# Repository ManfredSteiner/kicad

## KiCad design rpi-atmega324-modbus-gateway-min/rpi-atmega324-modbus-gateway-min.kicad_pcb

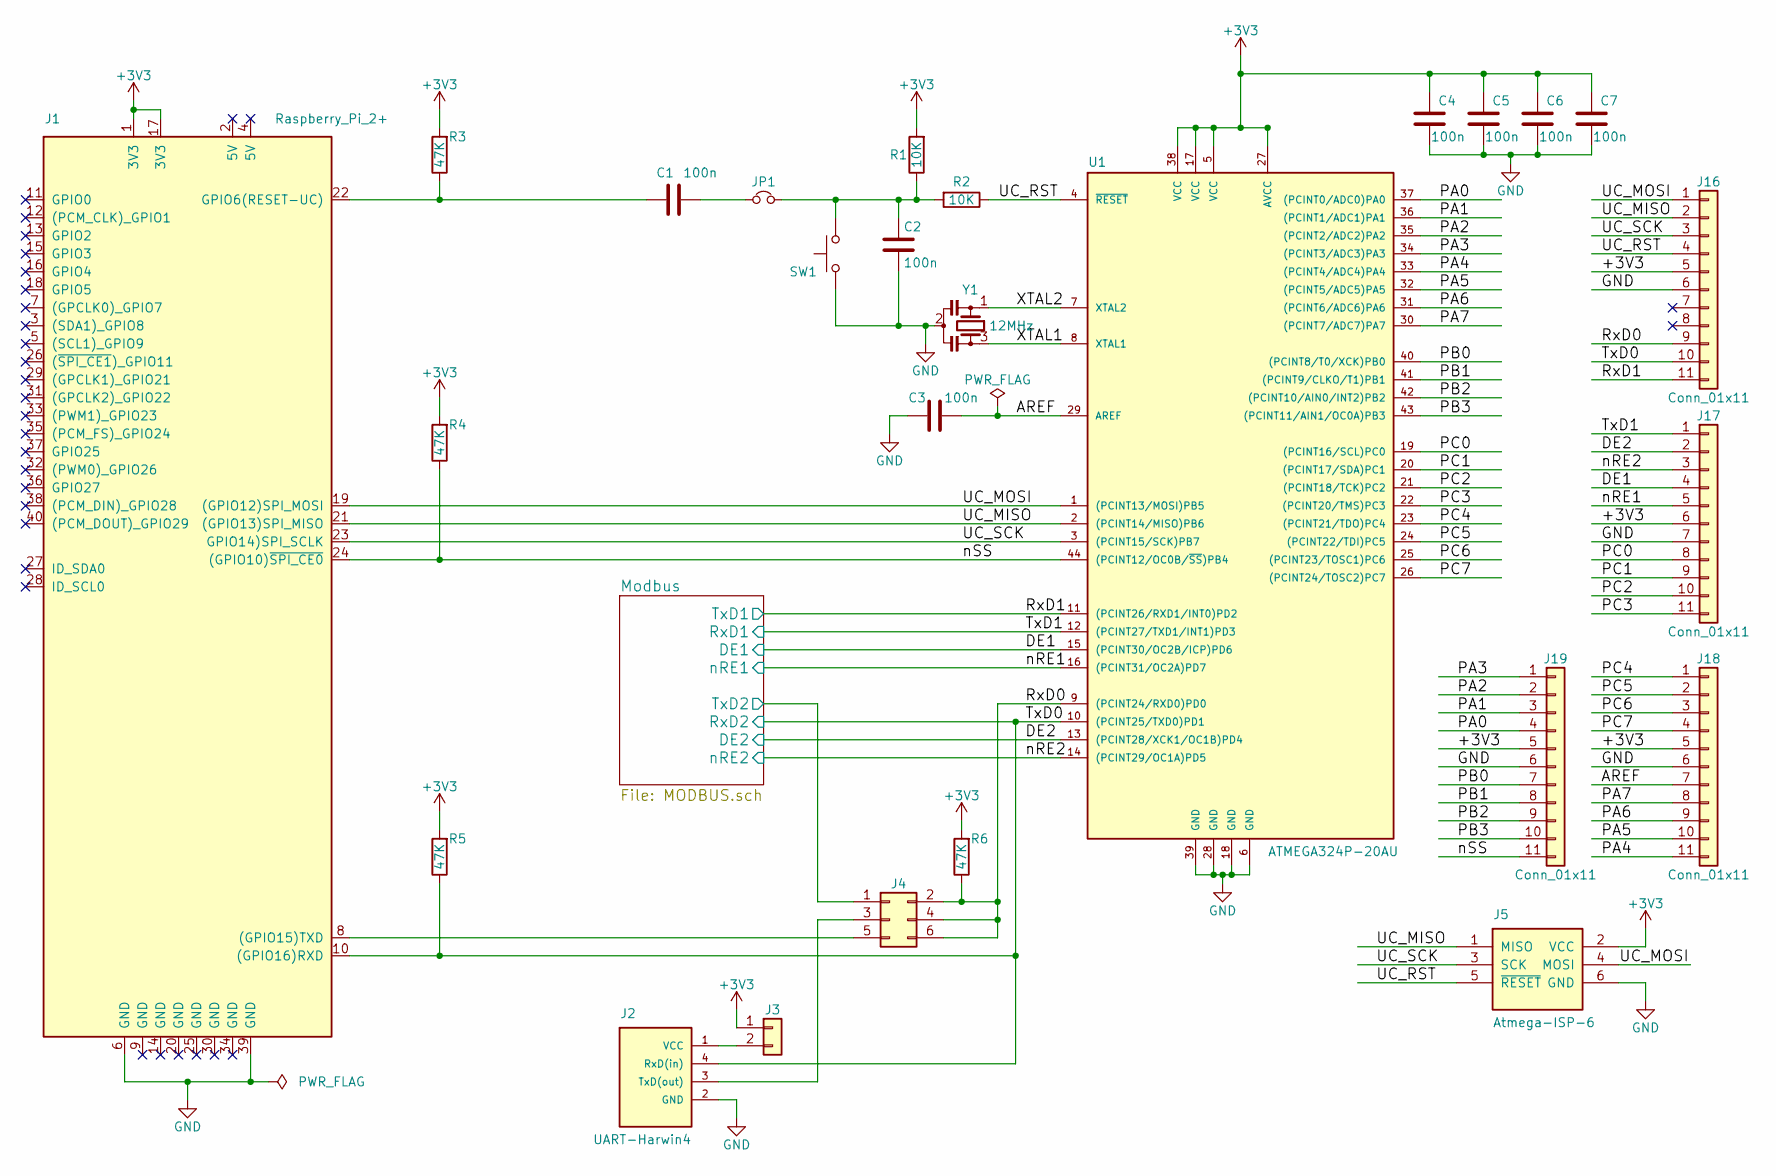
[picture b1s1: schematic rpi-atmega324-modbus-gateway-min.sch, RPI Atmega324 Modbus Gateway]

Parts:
C1, C2, C3, C4, C5, C6, C7: 100n; C_1206_HandSoldering
J1: Raspberry_Pi_2+; RPI_DINRAILBOX_4TE_72mmx91mm_DEBUG
J2: UART-Harwin4; Harwin_LTek-Male_04x2.00mm_Straight_StrainRelief
J3: Conn_01x02; Pin_Header_Straight_1x02_Pitch2.54mm
J4: Conn_02x03_Odd_Even; Pin_Header_Straight_2x03_Pitch2.54mm
J5: Atmega-ISP-6; IDC_2x3x2.54mm_Straight
J16, J17, J18, J19: Conn_01x11; Pin_Header_Straight_1x11_Pitch2.54mm
JP1: Jumper_NC_Small; SOLDER-JUMPER_1-WAY
R1, R2: 10K; R_1206_HandSoldering
R3, R4, R5, R6: 47K; R_1206_HandSoldering
SW1: SW_Push; SW_SPST_FSMSM
U1: ATMEGA324P-20AU; TQFP-44_10x10mm_Pitch0.8mm
Y1: 12MHz; Resonator-3pin_w7.0mm_h2.5mm

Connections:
+3V3: C4.2, C5.2, C6.2, C7.2, J1.1 (3V3), J1.17 (3V3), J3.1, J5.2 (VCC), J16.5, J17.6, J18.5, J19.5, R1.2, R3.2, R4.2, R5.2, R6.2, U1.5 (VCC), U1.17 (VCC), U1.27 (AVCC), U1.38 (VCC); also elsewhere on the board
/AREF: C3.1, J18.7, U1.29 (AREF)
/DE1: J17.4, U1.15 ((PCINT30/OC2B/ICP)PD6); also elsewhere on the board
/DE2: J17.2, U1.13 ((PCINT28/XCK1/OC1B)PD4); also elsewhere on the board
/Modbus/TxD2: J4.1; also elsewhere on the board
/PA0: J19.4, U1.37 ((PCINT0/ADC0)PA0)
/PA1: J19.3, U1.36 ((PCINT1/ADC1)PA1)
/PA2: J19.2, U1.35 ((PCINT2/ADC2)PA2)
/PA3: J19.1, U1.34 ((PCINT3/ADC3)PA3)
/PA4: J18.11, U1.33 ((PCINT4/ADC4)PA4)
/PA5: J18.10, U1.32 ((PCINT5/ADC5)PA5)
/PA6: J18.9, U1.31 ((PCINT6/ADC6)PA6)
/PA7: J18.8, U1.30 ((PCINT7/ADC7)PA7)
/PB0: J19.7, U1.40 ((PCINT8/T0/XCK)PB0)
/PB1: J19.8, U1.41 ((PCINT9/CLKO/T1)PB1)
/PB2: J19.9, U1.42 ((PCINT10/AIN0/INT2)PB2)
/PB3: J19.10, U1.43 ((PCINT11/AIN1/OC0A)PB3)
/PC0: J17.8, U1.19 ((PCINT16/SCL)PC0)
/PC1: J17.9, U1.20 ((PCINT17/SDA)PC1)
/PC2: J17.10, U1.21 ((PCINT18/TCK)PC2)
/PC3: J17.11, U1.22 ((PCINT20/TMS)PC3)
/PC4: J18.1, U1.23 ((PCINT21/TDO)PC4)
/PC5: J18.2, U1.24 ((PCINT22/TDI)PC5)
/PC6: J18.3, U1.25 ((PCINT23/TOSC1)PC6)
/PC7: J18.4, U1.26 ((PCINT24/TOSC2)PC7)
/RxD0: J4.2, J4.4, J4.6, J16.9, R6.1, U1.9 ((PCINT24/RXD0)PD0)
/RxD1: J16.11, U1.11 ((PCINT26/RXD1/INT0)PD2); also elsewhere on the board
/TxD0: J1.10 ((GPIO16)RXD), J2.4 (RxD(in)), J16.10, R5.1, U1.10 ((PCINT25/TXD0)PD1); also elsewhere on the board
/TxD1: J17.1, U1.12 ((PCINT27/TXD1/INT1)PD3); also elsewhere on the board
/UC_MISO: J1.21 ((GPIO13)SPI_MISO), J5.1 (MISO), J16.2, U1.2 ((PCINT14/MISO)PB6)
/UC_MOSI: J1.19 ((GPIO12)SPI_MOSI), J5.4 (MOSI), J16.1, U1.1 ((PCINT13/MOSI)PB5)
/UC_RST: J5.5 (~RESET~), J16.4, R2.1, U1.4 (~RESET)
/UC_SCK: J1.23 (GPIO14)SPI_SCLK), J5.3 (SCK), J16.3, U1.3 ((PCINT15/SCK)PB7)
/XTAL1: U1.8 (XTAL1), Y1.3
/XTAL2: U1.7 (XTAL2), Y1.1
/nRE1: J17.5, U1.16 ((PCINT31/OC2A)PD7); also elsewhere on the board
/nRE2: J17.3, U1.14 ((PCINT29/OC1A)PD5); also elsewhere on the board
/nSS: J1.24 ((GPIO10)~SPI_CE0~), J19.11, R4.1, U1.44 ((PCINT12/OC0B/~SS~)PB4)
GND: C2.2, C3.2, C4.1, C5.1, C6.1, C7.1, J1.6 (GND), J1.39 (GND), J2.2 (GND), J5.6 (GND), J16.6, J17.7, J18.6, J19.6, SW1.1, U1.6 (GND), U1.18 (GND), U1.28 (GND), U1.39 (GND), Y1.2; also elsewhere on the board
unnamed: C1.1, JP1.1
unnamed: C1.2, J1.22 (GPIO6(RESET-UC)), R3.1
unnamed: C2.1, JP1.2, R1.1, R2.2, SW1.2
unnamed: J1.8 ((GPIO15)TXD), J4.5
unnamed: J2.1 (VCC), J3.2
unnamed: J2.3 (TxD(out)), J4.3

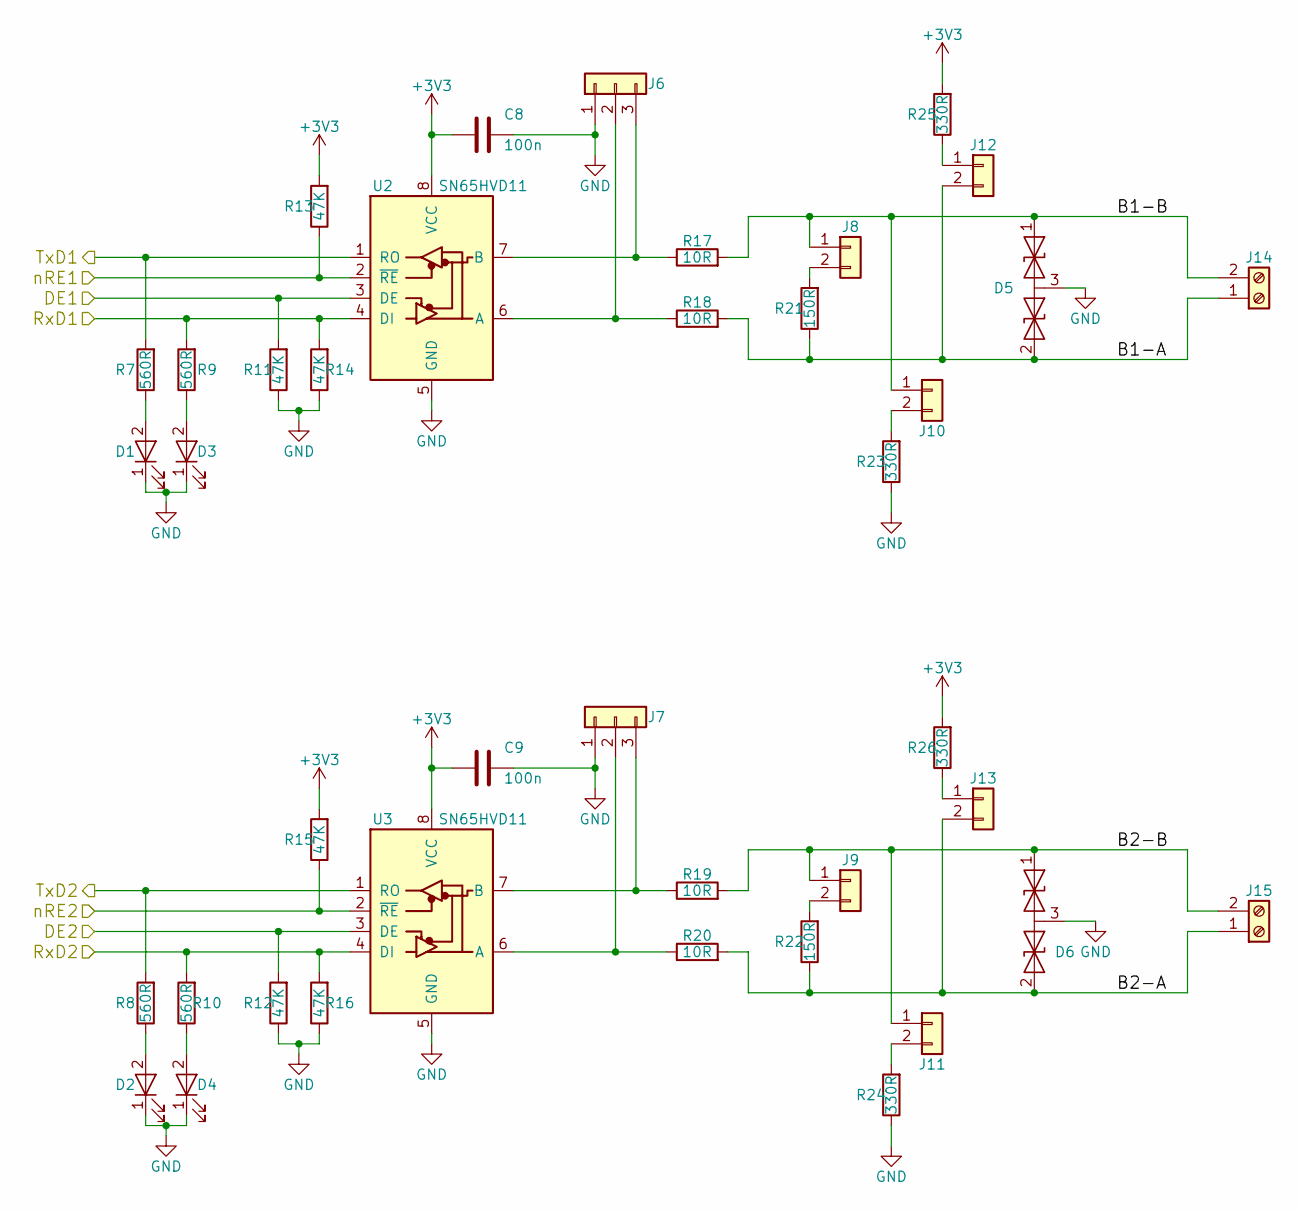
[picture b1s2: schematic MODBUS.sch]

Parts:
C8, C9: 100n; C_1206_HandSoldering
D1, D2, D3, D4: LED; LED_0805_HandSoldering
D5, D6: D_TVS_x2_AAC; SOT-23_Handsoldering
J6, J7: Conn_01x03; Pin_Header_Straight_1x03_Pitch2.54mm
J8, J9, J10, J11, J12, J13: Conn_01x02; Pin_Header_Straight_1x02_Pitch2.54mm
J14, J15: Screw_Terminal_01x02; Terminalblock-2x-5mm
R7, R8, R9, R10: 560R; R_1206_HandSoldering
R11, R12, R13, R14, R15, R16: 47K; R_1206_HandSoldering
R17, R18, R19, R20: 10R; R_1206_HandSoldering
R21, R22: 150R; R_1206_HandSoldering
R23, R24, R25, R26: 330R; R_1206_HandSoldering
U2, U3: SN65HVD11; SOIC-8_3.9x4.9mm_Pitch1.27mm

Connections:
+3V3: C8.2, C9.2, R13.2, R15.2, R25.2, R26.2, U2.8 (VCC), U3.8 (VCC); also elsewhere on the board
/DE1: R11.2, U2.3 (DE); also elsewhere on the board
/DE2: R12.2, U3.3 (DE); also elsewhere on the board
/Modbus/B1-A: D5.2 (A2), J12.2, J14.1, R18.2, R21.1
/Modbus/B1-B: D5.1 (A1), J8.1, J10.1, J14.2, R17.2
/Modbus/B2-A: D6.2 (A2), J13.2, J15.1, R20.2, R22.1
/Modbus/B2-B: D6.1 (A1), J9.1, J11.1, J15.2, R19.2
/Modbus/TxD2: R8.2, U3.1 (RO); also elsewhere on the board
/RxD1: R7.2, U2.1 (RO); also elsewhere on the board
/TxD0: R10.2, R16.2, U3.4 (DI); also elsewhere on the board
/TxD1: R9.2, R14.2, U2.4 (DI); also elsewhere on the board
/nRE1: R13.1, U2.2 (~RE); also elsewhere on the board
/nRE2: R15.1, U3.2 (~RE); also elsewhere on the board
GND: C8.1, C9.1, D1.1 (K), D2.1 (K), D3.1 (K), D4.1 (K), D5.3 (common), D6.3 (common), J6.1, J7.1, R11.1, R12.1, R14.1, R16.1, R23.1, R24.1, U2.5 (GND), U3.5 (GND); also elsewhere on the board
unnamed: D1.2 (A), R7.1
unnamed: D2.2 (A), R8.1
unnamed: D3.2 (A), R9.1
unnamed: D4.2 (A), R10.1
unnamed: J6.2, R18.1, U2.6 (A)
unnamed: J6.3, R17.1, U2.7 (B)
unnamed: J7.2, R20.1, U3.6 (A)
unnamed: J7.3, R19.1, U3.7 (B)
unnamed: J8.2, R21.2
unnamed: J9.2, R22.2
unnamed: J10.2, R23.2
unnamed: J11.2, R24.2
unnamed: J12.1, R25.1
unnamed: J13.1, R26.1

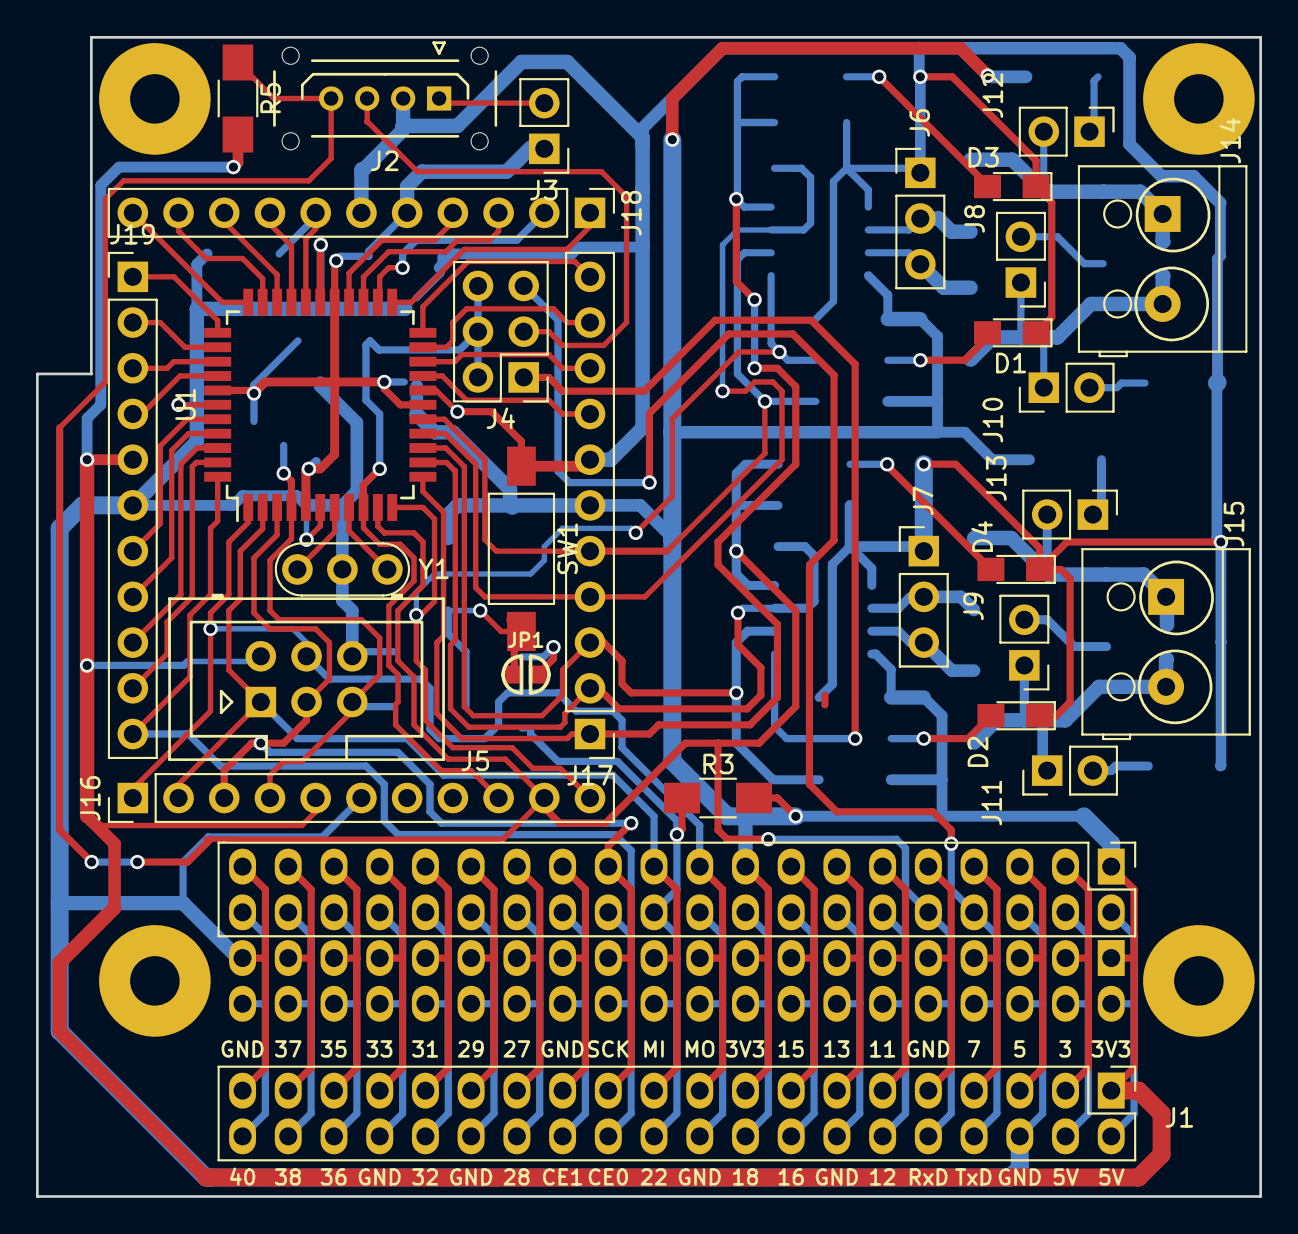
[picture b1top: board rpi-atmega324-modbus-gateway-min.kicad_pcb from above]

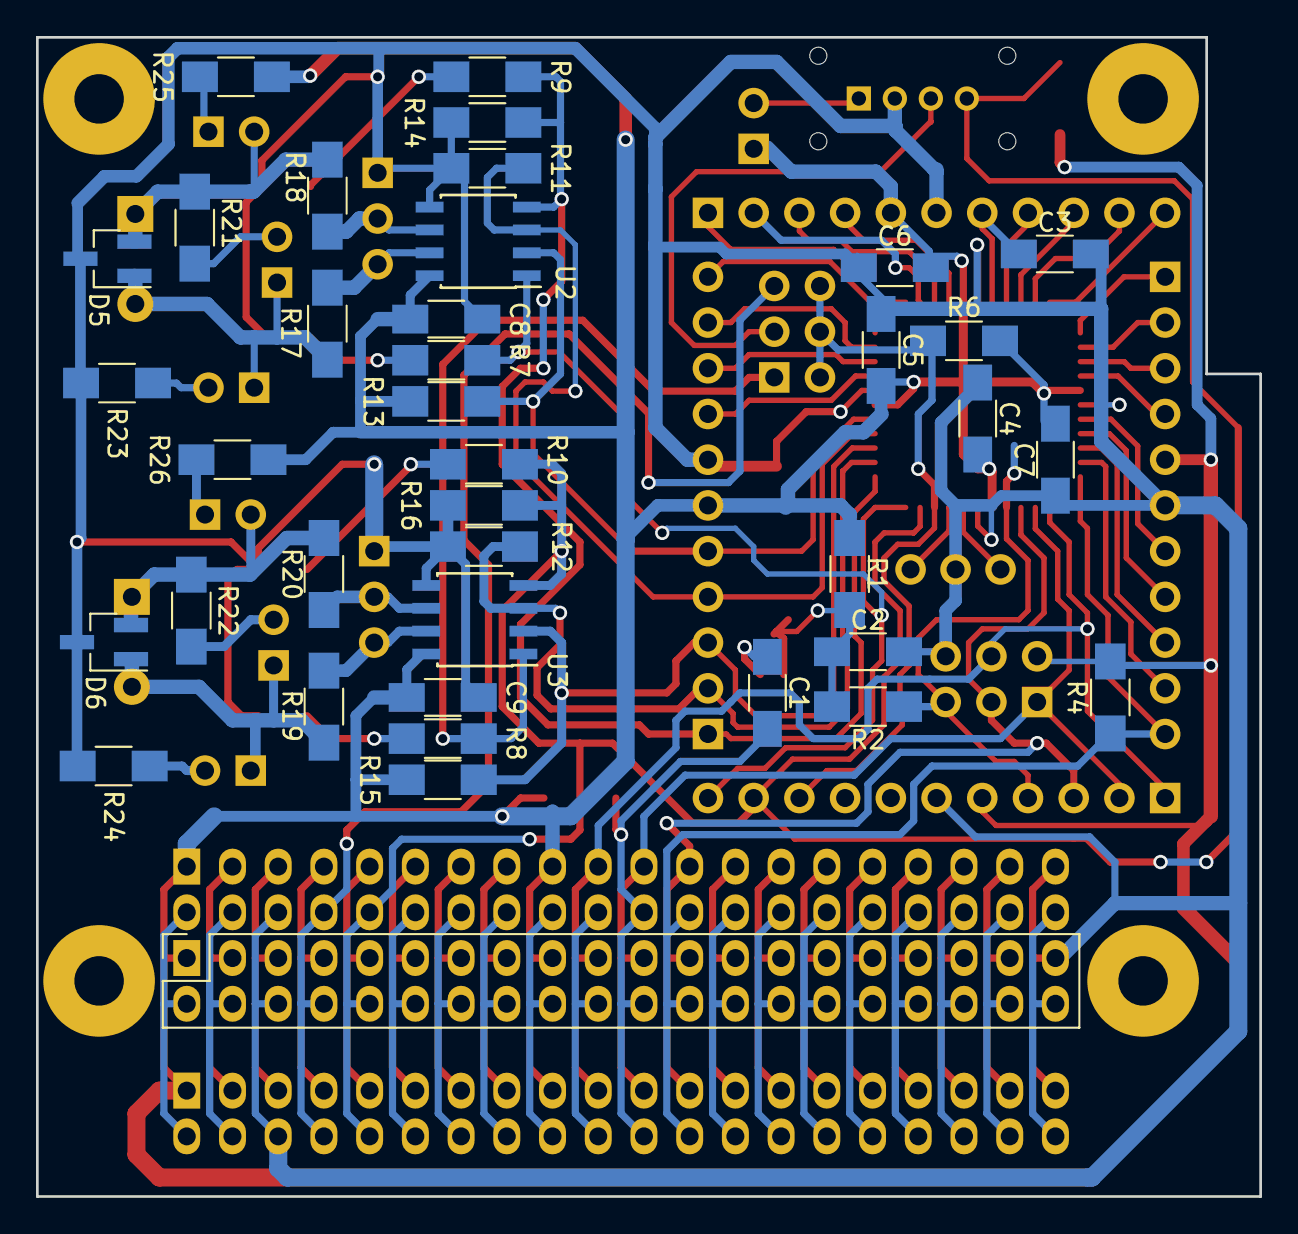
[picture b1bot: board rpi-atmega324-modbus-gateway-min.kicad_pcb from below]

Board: 2 copper layers, 68.0 x 64.4 mm, 66 parts (37 on the bottom side), 63 nets.

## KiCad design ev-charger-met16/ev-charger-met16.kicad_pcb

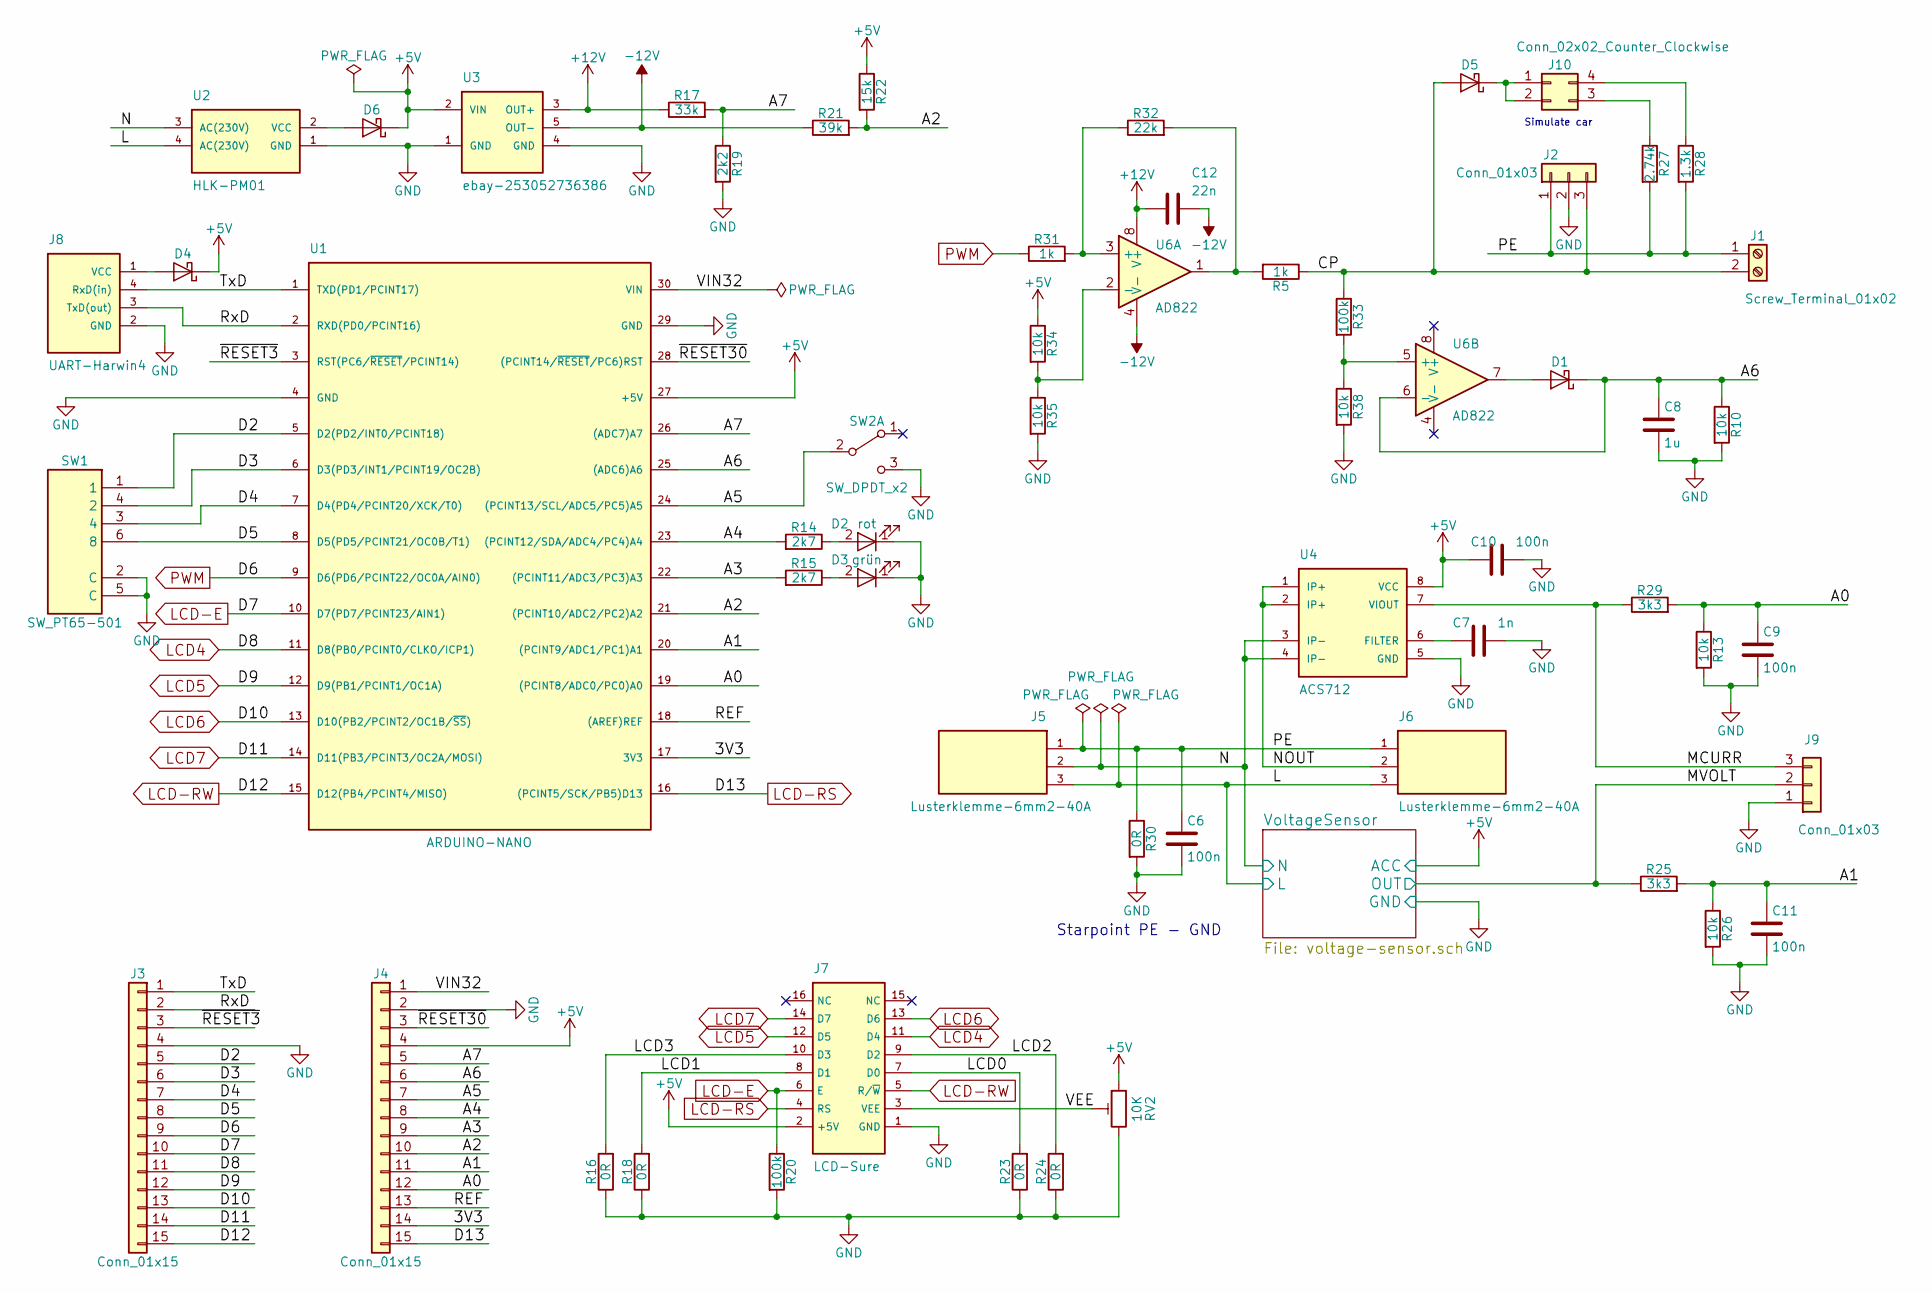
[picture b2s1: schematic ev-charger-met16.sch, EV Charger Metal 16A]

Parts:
C6, C9, C10, C11: 100n; C_1206_HandSoldering
C7: 1n; C_1206_HandSoldering
C8: 1u; C_1206_HandSoldering
C12: 22n; C_1206_HandSoldering
D1, D4, D5: D_Schottky; D_SOD-323_HandSoldering
D2: rot; LED_PLCC-2
D3: grün; LED_PLCC-2
D6: D_Schottky; D_SMA-SMB_Universal_Handsoldering
J1: Screw_Terminal_01x02; Terminalblock-2x-5mm
J2, J9: Conn_01x03; Pin_Header_Straight_1x03_Pitch2.54mm
J3, J4: Conn_01x15; Pin_Header_Straight_1x15_Pitch2.54mm
J5: Lusterklemme-6mm2-40A; Lusterklemme-PA30P-6mm2-40A-x3-N
J6: Lusterklemme-6mm2-40A; Lusterklemme-PA30P-6mm2-40A-x3-S
J7: LCD-Sure; LCD-Sure-shifted-064
J8: UART-Harwin4; Harwin_LTek-Male_04x2.00mm_Straight_StrainRelief
J10: Conn_02x02_Counter_Clockwise; Pin_Header_Straight_2x02_Pitch2.54mm
R5, R31: 1k; R_1206_HandSoldering
R10, R13, R26, R34, R35, R38: 10k; R_1206_HandSoldering
R14, R15: 2k7; R_1206_HandSoldering
R16, R18, R23, R24, R30: 0R; R_1206_HandSoldering
R17: 33k; R_1206_HandSoldering
R19: 2k2; R_1206_HandSoldering
R20, R33: 100k; R_1206_HandSoldering
R21: 39k; R_1206_HandSoldering
R22: 15k; R_1206_HandSoldering
R25, R29: 3k3; R_1206_HandSoldering
R27: 2.74k; R_1206_HandSoldering
R28: 1.3k; R_1206_HandSoldering
R32: 22k; R_1206_HandSoldering
RV2: 10K; Potentiometer_Trimmer_Bourns_3296W
SW1: SW_PT65-501; SW_DIP_x3_W7.62mm_PT65-501
SW2: SW_DPDT_x2; SW-ebay-171865305033
U1: ARDUINO-NANO; Arduino-Nano
U2: HLK-PM01; HLK_PM01
U3: ebay-253052736386
U4: ACS712; SO-8_5.3x6.2mm_Pitch1.27mm
U6: AD822; SO-8_5.3x6.2mm_Pitch1.27mm

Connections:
+5V: C10.2, D4.1 (K), D6.1 (K), J4.4, J7.2 (+5V), R22.1, R34.1, RV2.1, U1.27 (+5V), U3.2 (VIN), U4.8 (VCC); also elsewhere on the board
+12V: C12.2, R17.1, U3.3 (OUT+), U6.8 (V+)
-12V: C12.1, R21.1, U3.5 (OUT-), U6.4 (V-)
/3V3: J4.14, U1.17 (3V3)
/A0: C9.1, J4.12, R13.1, R29.2, U1.19 ((PCINT8/ADC0/PC0)A0)
/A1: C11.1, J4.11, R25.2, R26.1, U1.20 ((PCINT9/ADC1/PC1)A1)
/A2: J4.10, R21.2, R22.2, U1.21 ((PCINT10/ADC2/PC2)A2)
/A3: J4.9, R15.2, U1.22 ((PCINT11/ADC3/PC3)A3)
/A4: J4.8, R14.2, U1.23 ((PCINT12/SDA/ADC4/PC4)A4)
/A5: J4.7, SW2.2 (B), U1.24 ((PCINT13/SCL/ADC5/PC5)A5)
/A6: C8.1, D1.1 (K), J4.6, R10.1, U1.25 ((ADC6)A6), U6.6 (-)
/A7: J4.5, R17.2, R19.1, U1.26 ((ADC7)A7)
/CP: D5.2 (A), J1.2, J2.3, R5.1, R33.1
/D2: J3.5, SW1.1, U1.5 (D2(PD2/INT0/PCINT18))
/D3: J3.6, SW1.4 (2), U1.6 (D3(PD3/INT1/PCINT19/OC2B))
/D4: J3.7, SW1.3 (4), U1.7 (D4(PD4/PCINT20/XCK/T0))
/D5: J3.8, SW1.6 (8), U1.8 (D5(PD5/PCINT21/OC0B/T1))
/L: J5.3, J6.3, U2.4 (AC(230V)); also elsewhere on the board
/LCD0: J7.7 (D0), R23.2
/LCD1: J7.8 (D1), R18.2
/LCD2: J7.9 (D2), R24.2
/LCD3: J7.10 (D3), R16.2
/MCURR: J9.3, R29.1, U4.7 (VIOUT)
/MVOLT: J9.2, R25.1; also elsewhere on the board
/N: J5.2, U2.3 (AC(230V)), U4.3 (IP-), U4.4 (IP-); also elsewhere on the board
/NOUT: J6.2, U4.1 (IP+), U4.2 (IP+)
/PE: C6.1, J1.1, J2.1, J5.1, J6.1, R27.2, R28.2, R30.1
/REF: J4.13, U1.18 ((AREF)REF)
/RxD: J3.2, J8.3 (TxD(out)), U1.2 (RXD(PD0/PCINT16))
/TxD: J3.1, J8.4 (RxD(in)), U1.1 (TXD(PD1/PCINT17))
/VEE: J7.3 (VEE), RV2.2
/VIN32: J4.1, U1.30 (VIN)
/~RESET3~: J3.3, U1.3 (RST(PC6/~RESET~/PCINT14))
/~RESET30~: J4.3, U1.28 ((PCINT14/~RESET~/PC6)RST)
GND: C6.2, C7.1, C8.2, C9.2, C10.1, C11.2, D2.1 (K), D3.1 (K), J2.2, J3.4, J4.2, J7.1 (GND), J8.2 (GND), J9.1, R10.2, R13.2, R16.1, R18.1, R19.2, R20.2, R23.1, R24.1, R26.2, R30.2, R35.2, R38.2, RV2.3, SW1.2 (C), SW1.5 (C), SW2.3 (C), U1.4 (GND), U1.29 (GND), U2.1 (GND), U3.1 (GND), U3.4 (GND), U4.5 (GND); also elsewhere on the board
LCD4: J3.11, J7.11 (D4), U1.11 (D8(PB0/PCINT0/CLKO/ICP1))
LCD5: J3.12, J7.12 (D5), U1.12 (D9(PB1/PCINT1/OC1A))
LCD6: J3.13, J7.13 (D6), U1.13 (D10(PB2/PCINT2/OC1B/~SS~))
LCD7: J3.14, J7.14 (D7), U1.14 (D11(PB3/PCINT3/OC2A/MOSI))
LCD-E: J3.10, J7.6 (E), R20.1, U1.10 (D7(PD7/PCINT23/AIN1))
LCD-RS: J4.15, J7.4 (RS), U1.16 ((PCINT5/SCK/PB5)D13)
LCD-RW: J3.15, J7.5 (R/~W~), U1.15 (D12(PB4/PCINT4/MISO))
unnamed: C7.2, U4.6 (FILTER)
unnamed: D1.2 (A), U6.7
unnamed: D2.2 (A), R14.1
unnamed: D3.2 (A), R15.1
unnamed: D4.2 (A), J8.1 (VCC)
unnamed: D5.1 (K), J10.1, J10.2
unnamed: D6.2 (A), U2.2 (VCC)
unnamed: J10.3, R27.1
unnamed: J10.4, R28.1
unnamed: R31.2, R32.1, U6.3 (+)
unnamed: R5.2, R32.2, U6.1
unnamed: R33.2, R38.1, U6.5 (+)
unnamed: R34.2, R35.1, U6.2 (-)
PWM: J3.9, R31.1, U1.9 (D6(PD6/PCINT22/OC0A/AIN0))

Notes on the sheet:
Starpoint PE - GND
Simulate car

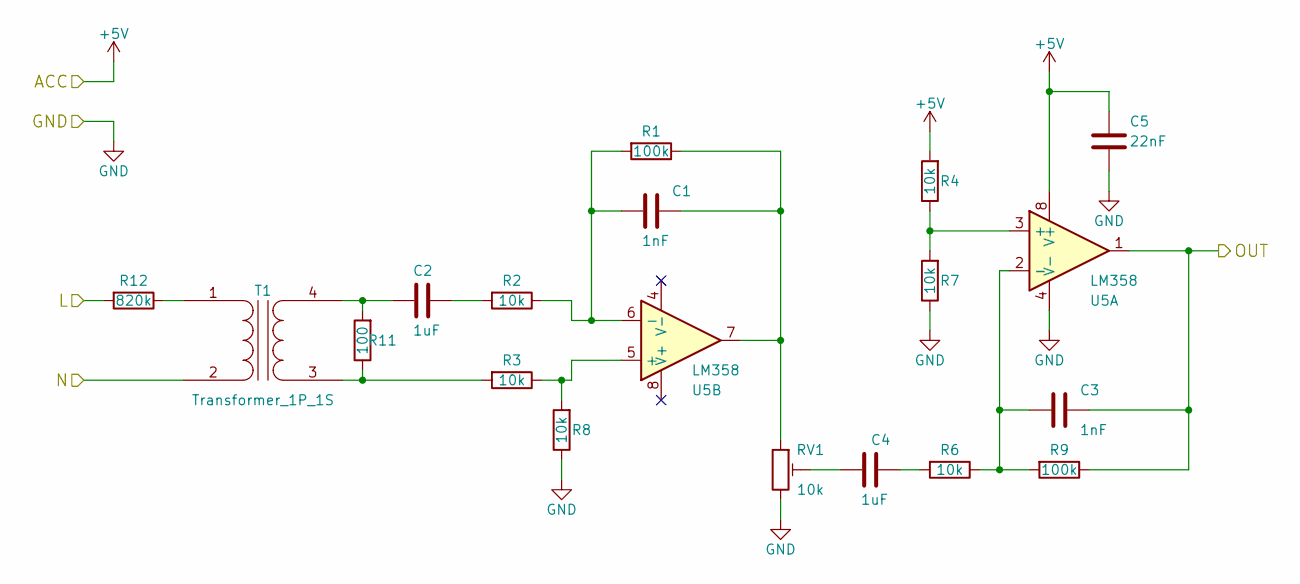
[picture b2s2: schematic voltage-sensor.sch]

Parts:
C1, C3: 1nF; C_1206_HandSoldering
C2, C4: 1uF; C_1206_HandSoldering
C5: 22nF; C_1206_HandSoldering
R1, R9: 100k; R_1206_HandSoldering
R2, R3, R4, R6, R7, R8: 10k; R_1206_HandSoldering
R11: 100; R_1206_HandSoldering
R12: 820k; R_1206_HandSoldering
RV1: 10k; Potentiometer_Trimmer_Bourns_3296W
T1: Transformer_1P_1S; Transformer-zmpt101b_ebay-121438904988
U5: LM358; SO-8_5.3x6.2mm_Pitch1.27mm

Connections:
+5V: C5.1, R4.2, U5.8 (V+); also elsewhere on the board
/L: R12.2; also elsewhere on the board
/MVOLT: C3.1, R9.1, U5.1; also elsewhere on the board
/N: T1.2 (AB); also elsewhere on the board
GND: C5.2, R7.1, R8.1, RV1.3, U5.4 (V-); also elsewhere on the board
unnamed: C1.1, R1.1, RV1.1, U5.7
unnamed: C1.2, R1.2, R2.1, U5.6 (-)
unnamed: C2.1, R2.2
unnamed: C2.2, R11.2, T1.4 (SB)
unnamed: C3.2, R6.1, R9.2, U5.2 (-)
unnamed: C4.1, R6.2
unnamed: C4.2, RV1.2
unnamed: R3.1, R8.2, U5.5 (+)
unnamed: R4.1, R7.2, U5.3 (+)
unnamed: R3.2, R11.1, T1.3 (SA)
unnamed: R12.1, T1.1 (AA)

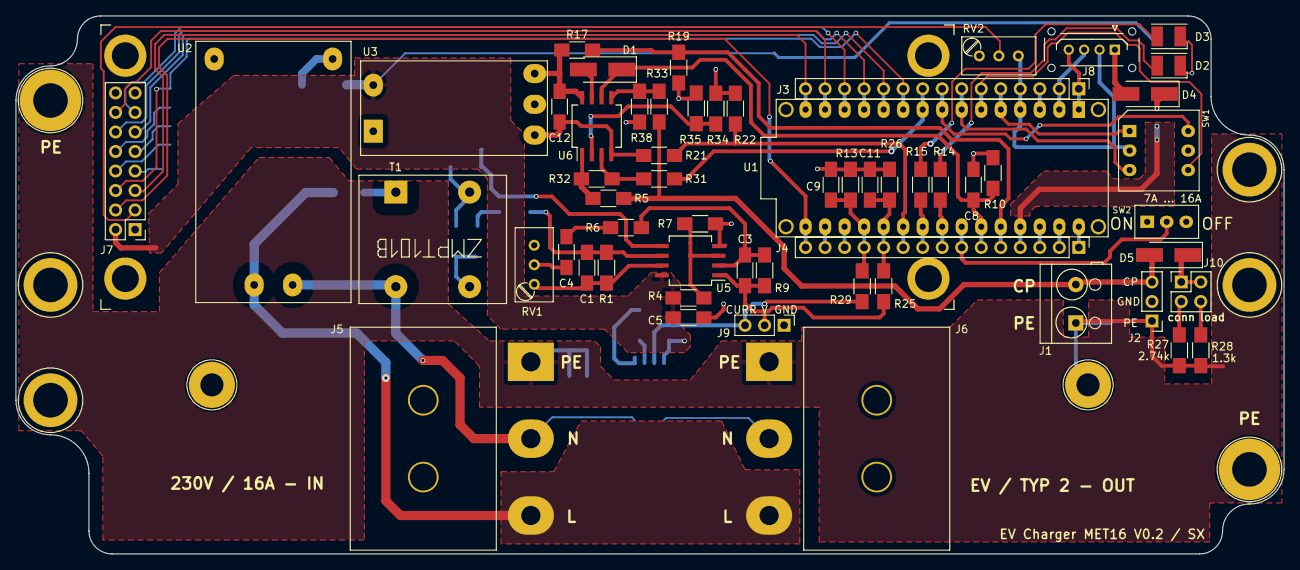
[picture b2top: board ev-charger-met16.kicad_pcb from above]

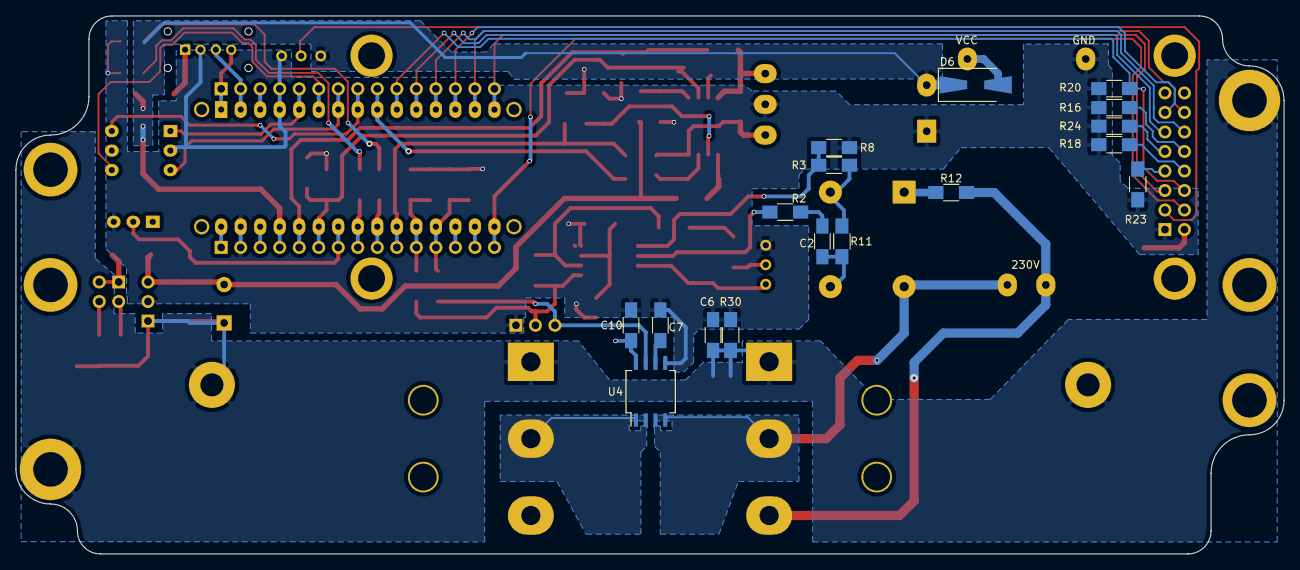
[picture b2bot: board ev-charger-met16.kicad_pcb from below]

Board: 2 copper layers, 165.0 x 70.0 mm, 75 parts (17 on the bottom side), 67 nets.

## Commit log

2018-05-15 Erster Entwurf V0.2
2018-05-17 V0.2 Design finished
2018-05-27 Version V0.2 - ready for multi-cb
2018-05-27 removing old schematic pdf
2018-05-31 Gerber file fix for manufactering ev-charger-met16 V0.2
2018-06-07 modbus-gateway-min first design finished, optimization needed
2018-06-10 Modbus Gateway V0.1 - Tapeout 1
2018-06-15 First software (under construction
2018-06-17 EV charger first version tested on car
2018-06-17 software hex file added to dist folder
2018-06-23 software - first spi transfer
2018-06-24 software for SPI, protocol working
2018-06-30 Software 1xUart 1xModbus
2018-06-30 Software change 2xModbus 1xSPI
2018-07-12 rpi-ts-froniusmeter V0.3
2018-07-12 rpi-ts-froniusmeter, separated to server
2018-07-12 rpi-ts-froniusmeter: server/client
2018-07-14 rpi-ts-froniusmeter V 0.4 (Angular App, Chart)
2018-07-17 rpi-ts-froniusmeter
2018-07-18 Fronius Symo Modbus register on Web
2018-07-23 Home Control - alle Messungen
2018-07-23 rpi-ts V0.7.0
2018-08-02 rpi software
2018-08-05 sx-relais kicad library added
2018-08-09 statistics changes
2018-08-11 change to atmega328 gateway-simple
2018-08-12 bugfix
2018-08-26 including Nibe1155
2018-08-28 controlling heat pump
2018-10-01 debug fronius inverter
2018-10-18 V0.15.0, bugfix
2018-10-18 V0.16.0@rpi-atmega324-modbus-gateway-mi: bugfix
2018-12-01 change froniusmeter
2018-12-02 change froniusmeter -> history
2018-12-02 webclient overview improvement
